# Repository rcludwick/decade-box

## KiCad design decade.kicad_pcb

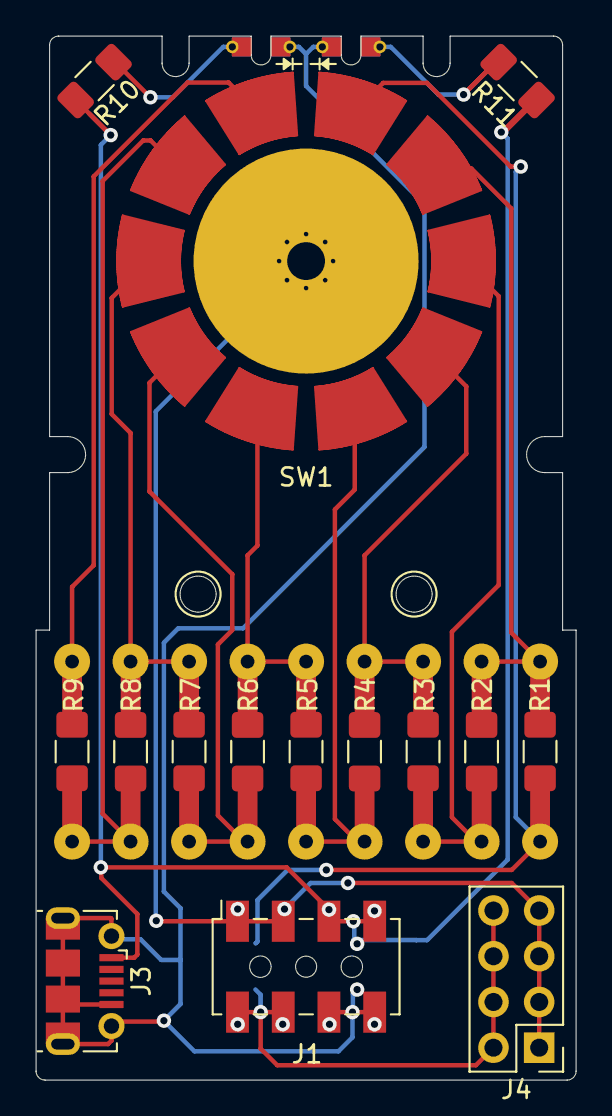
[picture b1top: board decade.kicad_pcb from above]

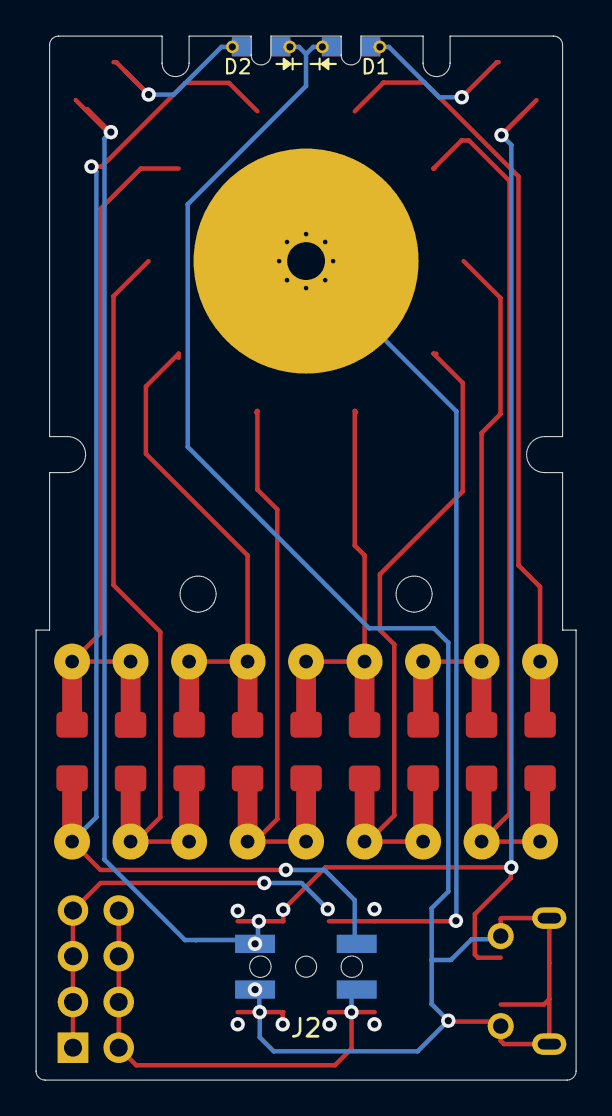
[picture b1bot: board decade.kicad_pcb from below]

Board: 2 copper layers, 30.0 x 58.0 mm, 20 parts (3 on the bottom side), 16 nets.

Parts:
2.1MM, 2.1MM#2: NPTH_2.1MM
D1, D2: LED; 0603_LED_Bottom_Entry
J1: Conn_02x04_Odd_Even; Samtec_HLE-104-02-xxx-DV-LC_2x04_P2.54mm_Horizontal
J2: Conn_02x02_Odd_Even; SSM-102-F-DV-A
J3: USB_B_Micro; USB_Micro-B_Molex-105017-0001
J4: Conn_02x04_Odd_Even; PinHeader_2x04_P2.54mm_Vertical
R1, R2, R3, R4, R5, R6, R7, R8, R9: R; R_1206_10mm_combo
R10, R11: R; R_1206_3216Metric_Pad1.42x1.75mm_HandSolder
SW1: SW_ROTARY_10_POS; thumbwheel-1

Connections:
+5V: J1.5, J1.7, J2.2, J3.1, R10.1, R11.1
/IN: J1.1, J1.3, J4.1, J4.3, J4.5, J4.7, SW1.C
/OUT: J2.1, R1.2, SW1.0
/THRU: J1.2, J1.4, J2.3, J4.2, J4.4, J4.6, J4.8
GND: D1.1, D2.1, J1.6, J1.8, J2.4, J3.5, J3.6
unnamed: D1.2, R10.2
unnamed: D2.2, R11.2
unnamed: R1.1, R2.2, SW1.1
unnamed: R2.1, R3.2, SW1.2
unnamed: R3.1, R4.2, SW1.3
unnamed: R4.1, R5.2, SW1.4
unnamed: R5.1, R6.2, SW1.5
unnamed: R6.1, R7.2, SW1.6
unnamed: R7.1, R8.2, SW1.7
unnamed: R8.1, R9.2, SW1.8
unnamed: R9.1, SW1.9

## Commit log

2020-11-27 Minor updates including gerbers.
